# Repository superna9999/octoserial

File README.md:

# OctoSerial

USB High-Speed to 8x RS-232 TTL level with the CH348Q IC.

Schematics: [octoserial.pdf](octoserial.pdf)

Changelog
---------

Version 1.1:
- Production version with 40pins headers with GPIOs + 3v3 + VBUS & GND

Version 0.1:
- Initial prototype with CH348Q samples

LICENCE
-------

```
Apache License Version 2.0
```

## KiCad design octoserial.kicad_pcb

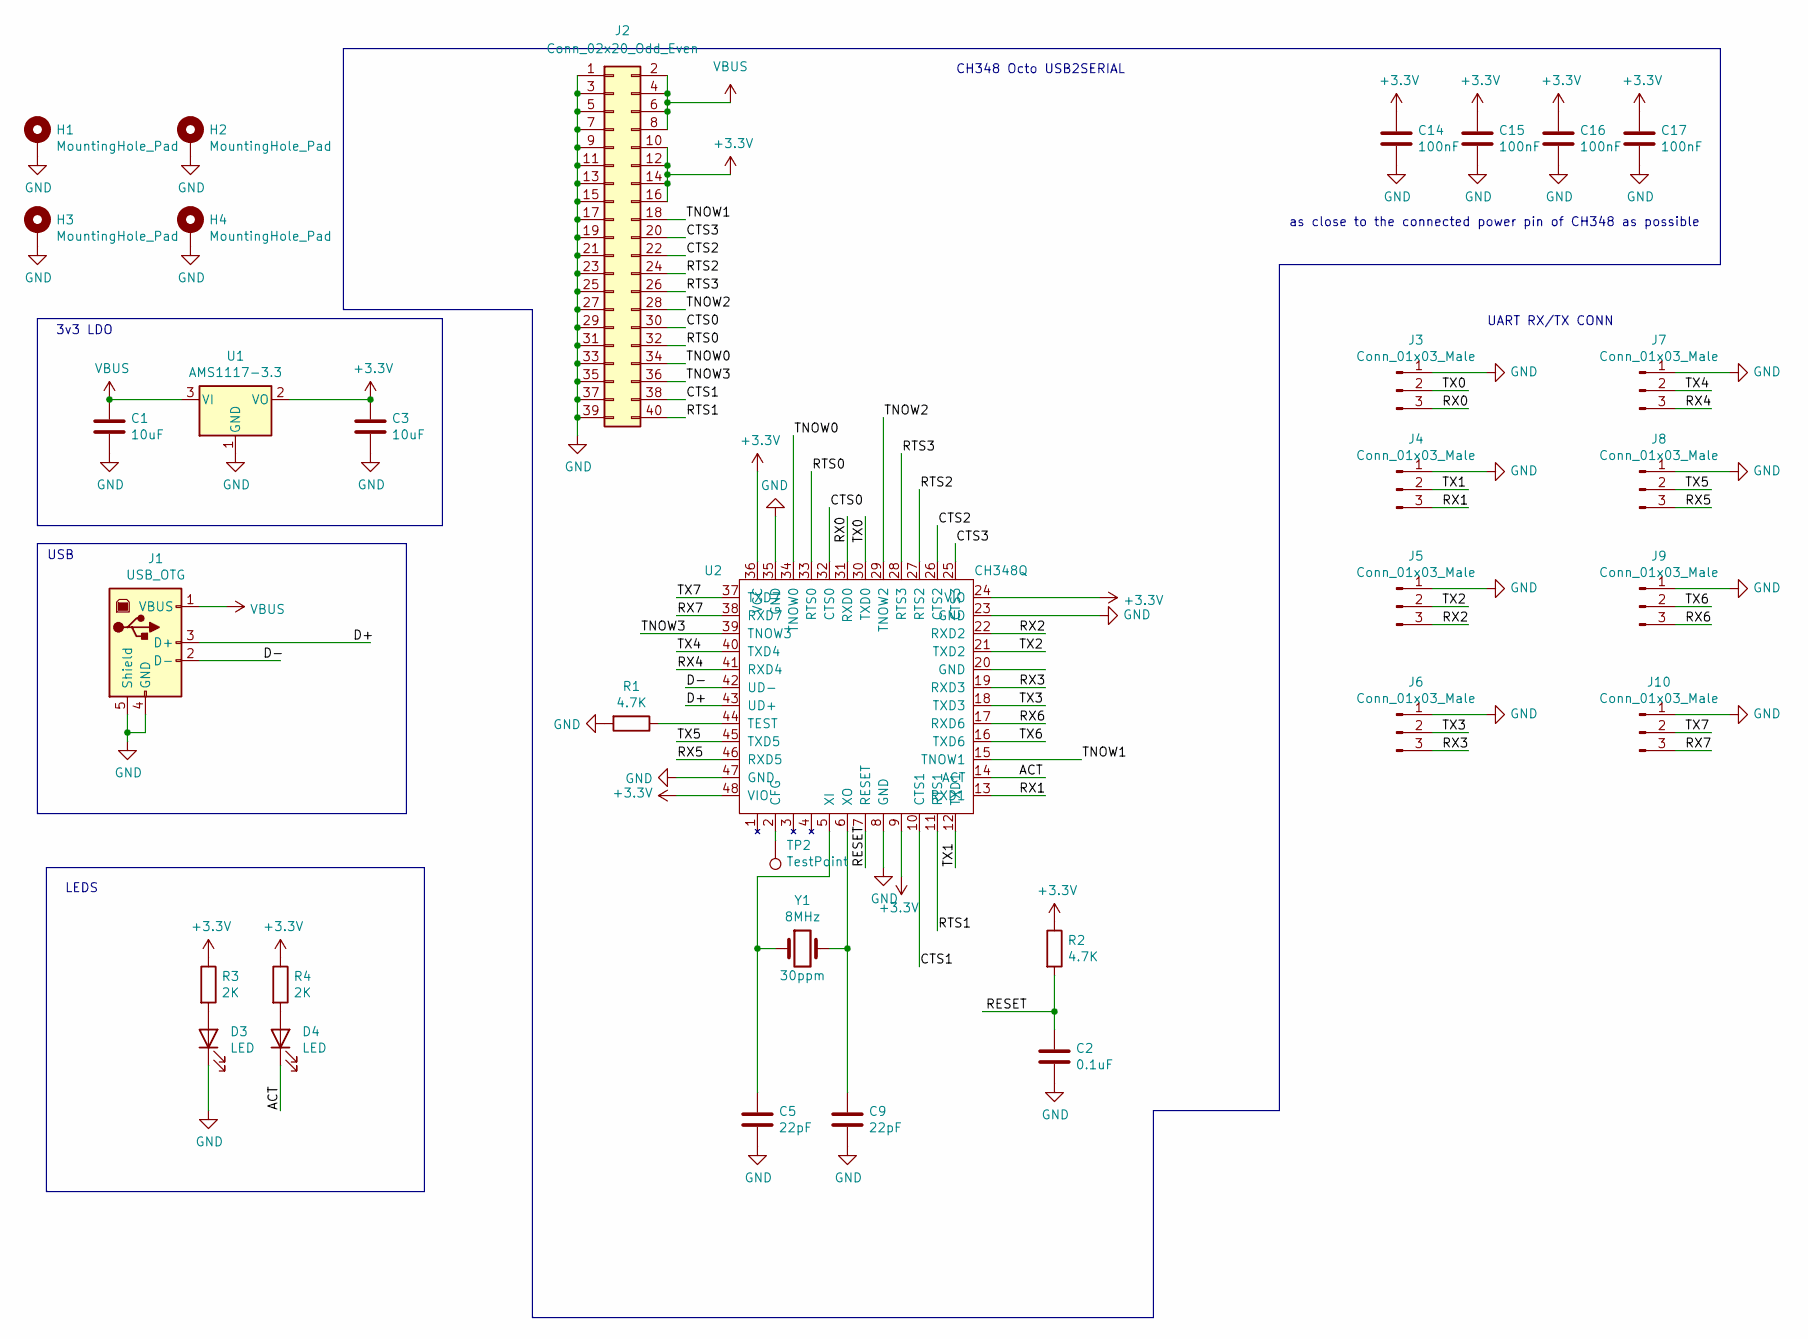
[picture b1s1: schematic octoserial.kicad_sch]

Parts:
C1, C3: 10uF; C_1206_3216Metric_Pad1.33x1.80mm_HandSolder; JLC 1206
C2: 0.1uF; C_1206_3216Metric_Pad1.33x1.80mm_HandSolder; JLC 1206
C5, C9: 22pF; C_1206_3216Metric_Pad1.33x1.80mm_HandSolder; JLC 1206
C14, C15, C16, C17: 100nF; C_1206_3216Metric_Pad1.33x1.80mm_HandSolder; JLC 1206
D3, D4: LED; LED_1206_3216Metric_Pad1.42x1.75mm_HandSolder; JLC 1206
H1, H2, H3, H4: MountingHole_Pad; MountingHole_3.2mm_M3_Pad
J1: USB_OTG; USB_B_Lumberg_2411_02_Horizontal; LCSC C46392
J2: Conn_02x20_Odd_Even; PinHeader_2x20_P2.54mm_Vertical; LCSC C124383
J3, J4, J5, J6, J7, J8, J9, J10: Conn_01x03_Male; PinSocket_1x03_P2.54mm_Horizontal; LCSC C5116482
R1, R2: 4.7K; R_1206_3216Metric_Pad1.30x1.75mm_HandSolder; JLC 1206
R3, R4: 2K; R_1206_3216Metric_Pad1.30x1.75mm_HandSolder; JLC 1206
TP2: TestPoint; TestPoint_Pad_D1.0mm
U1: AMS1117-3.3; SOT-223-3_TabPin2; JLC SOT-223-3
U2: CH348Q; LQFP-48_7x7mm_P0.5mm; LCSC C2979161
Y1: 8MHz; Crystal_HC49-4H_Vertical; LCSC C21263

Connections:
+3V3: C3.1, C14.1, C15.1, C16.1, C17.1, J2.10, J2.12, J2.14, J2.16, R2.1, R3.1, R4.1, U1.2 (VO), U2.9, U2.24 (VIO), U2.36 (VCC), U2.48 (VIO)
/ACT: D4.1 (K), U2.14 (ACT)
/CTS0: J2.30, U2.32 (CTS0)
/CTS1: J2.38, U2.10 (CTS1)
/CTS2: J2.22, U2.26 (CTS2)
/CTS3: J2.20, U2.25 (CTS3)
/D+: J1.3 (D+), U2.43 (UD+)
/D-: J1.2 (D-), U2.42 (UD-)
/RESET: C2.1, R2.2, U2.7 (RESET)
/RTS0: J2.32, U2.33 (RTS0)
/RTS1: J2.40, U2.11 (RTS1)
/RTS2: J2.24, U2.27 (RTS2)
/RTS3: J2.26, U2.28 (RTS3)
/RX0: J3.3, U2.31 (RXD0)
/RX1: J4.3, U2.13 (RXD1)
/RX2: J5.3, U2.22 (RXD2)
/RX3: J6.3, U2.19 (RXD3)
/RX4: J7.3, U2.41 (RXD4)
/RX5: J8.3, U2.46 (RXD5)
/RX6: J9.3, U2.17 (RXD6)
/RX7: J10.3, U2.38 (RXD7)
/TNOW0: J2.34, U2.34 (TNOW0)
/TNOW1: J2.18, U2.15 (TNOW1)
/TNOW2: J2.28, U2.29 (TNOW2)
/TNOW3: J2.36, U2.39 (TNOW3)
/TX0: J3.2, U2.30 (TXD0)
/TX1: J4.2, U2.12 (TXD1)
/TX2: J5.2, U2.21 (TXD2)
/TX3: J6.2, U2.18 (TXD3)
/TX4: J7.2, U2.40 (TXD4)
/TX5: J8.2, U2.45 (TXD5)
/TX6: J9.2, U2.16 (TXD6)
/TX7: J10.2, U2.37 (TXD7)
GND: C1.2, C2.2, C3.2, C5.2, C9.2, C14.2, C15.2, C16.2, C17.2, D3.1 (K), H1.1, H2.1, H3.1, H4.1, J1.4 (GND), J1.5 (Shield), J2.1, J2.3, J2.5, J2.7, J2.9, J2.11, J2.13, J2.15, J2.17, J2.19, J2.21, J2.23, J2.25, J2.27, J2.29, J2.31, J2.33, J2.35, J2.37, J2.39, J3.1, J4.1, J5.1, J6.1, J7.1, J8.1, J9.1, J10.1, R1.2, U1.1 (GND), U2.8 (GND), U2.23 (GND), U2.35 (GND), U2.47 (GND)
unnamed: C5.1, U2.5 (XI), Y1.1
unnamed: C9.1, U2.6 (XO), Y1.2
unnamed: D3.2 (A), R3.2
unnamed: D4.2 (A), R4.2
unnamed: R1.1, U2.44 (TEST)
unnamed: TP2.1, U2.2 (CFG)
VBUS: C1.1, J1.1 (VBUS), J2.2, J2.4, J2.6, J2.8, U1.3 (VI)

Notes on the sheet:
LEDS
UART RX/TX CONN
3v3 LDO
USB
as close to the connected power pin of CH348 as possible
CH348 Octo USB2SERIAL

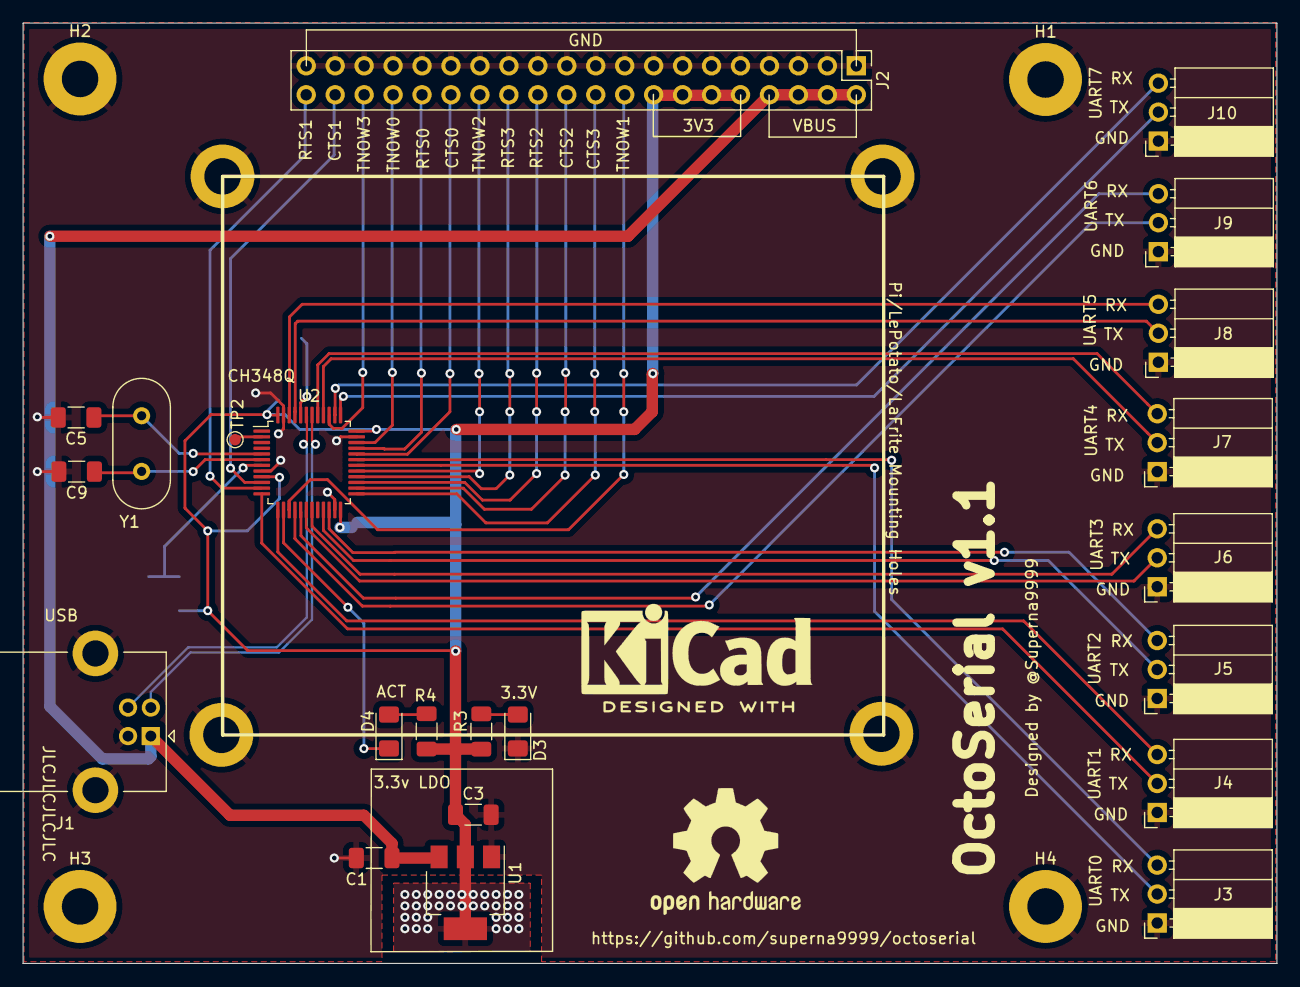
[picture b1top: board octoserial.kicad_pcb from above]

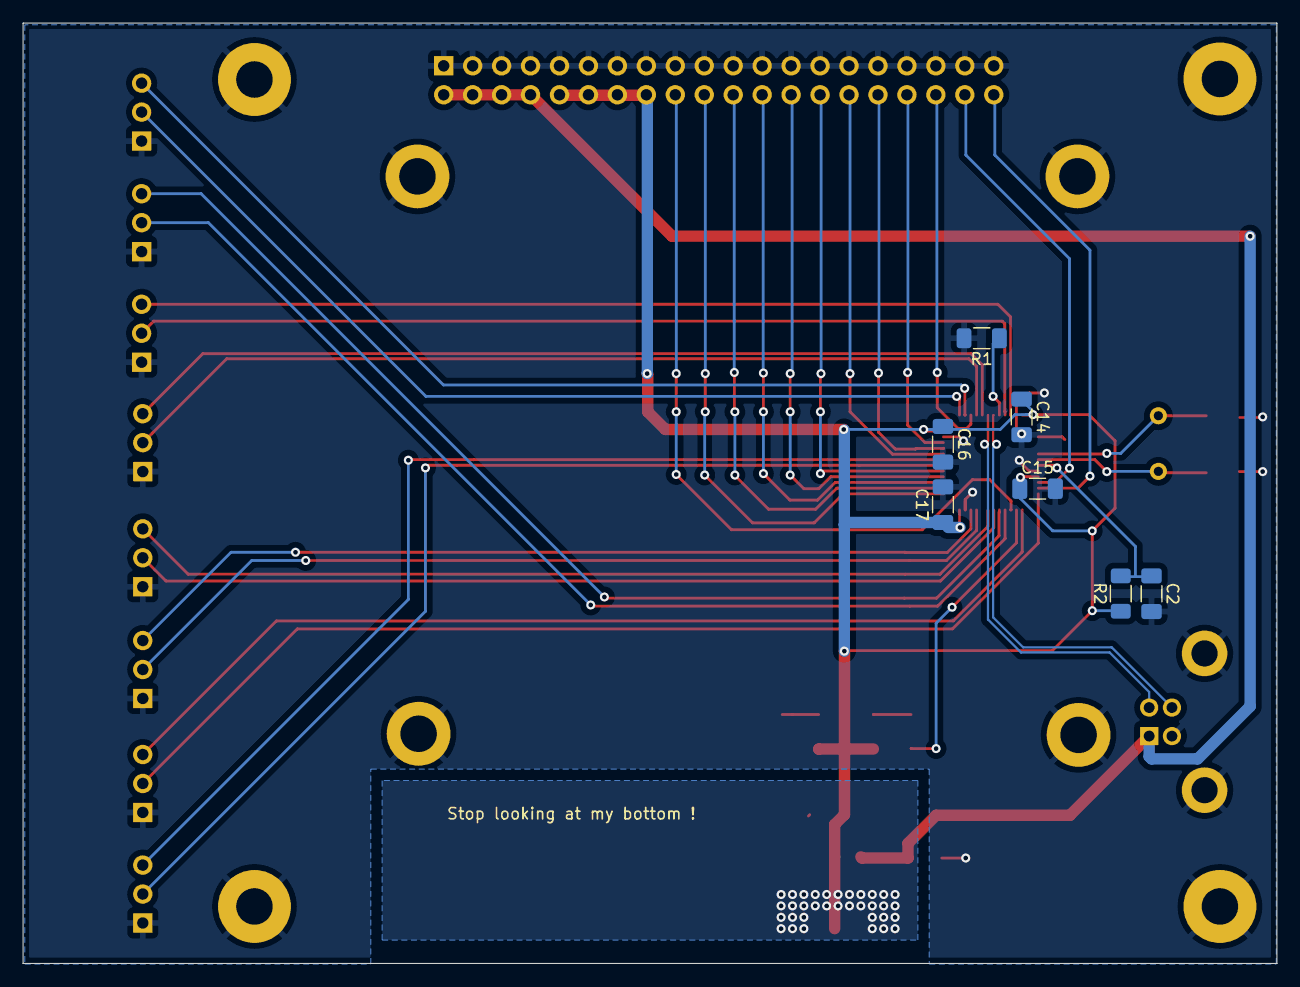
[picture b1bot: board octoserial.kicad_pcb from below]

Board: 2 copper layers, 110.0 x 82.5 mm, 33 parts (7 on the bottom side), 41 nets.

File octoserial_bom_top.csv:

"Comment","Designator","Footprint","LCSC Part #"
"10uF","C1 C3","1206","C13585"
"22pF","C5 C9","1206","C5137630"
"LED","D3","1206",""
"LED","D4","1206","C434438"
"USB_OTG","J1","","C46392"
"Conn_02x20_Odd_Even","J2","","C124383"
"Conn_01x03_Male","J3 J4 J5 J6 J7 J8 J9 J10","","C5116482"
"2K","R3 R4","1206","C17944"
"AMS1117-3.3","U1","SOT-223-3","C173386"
"CH348Q","U2","","C2979161"
"8MHz","Y1","","C21263"

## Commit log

2022-08-31 Import v0.1
2023-01-17 Add gpio/3.3 headers
2023-01-17 Add Kicad, OSHW + github URL on front silkscreen
2023-01-17 Add JPC & LCSC tags & regenerate gerber + bom CSVs
2023-01-17 Add README, pdf & image
